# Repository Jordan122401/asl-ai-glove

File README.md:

# AI-Powered Glove for ASL Translation

> ESP32 + sensor glove + Android app that streams hand-sensor data over Bluetooth and runs on-device ML to translate ASL gestures into text.

---

## 📋 Quick Links

- 📱 **Android app:** [`android/`](android/)
- 🧠 **Firmware (ESP32):** [`firmware/esp32/`](firmware/esp32/)
- 🧰 **Calibration tools (Python):** [`tools/`](tools/)
- 🧾 **Docs (BLE + setup + calibration):** [`docs/`](docs/)
- 🧩 **Hardware (schematics/PCB):** [`hardware/`](hardware/)

---

## 🎥 Demo

### Video Demonstration

### 📸 Project Gallery

#### SignCast Logo & App Interface

**Glove in Action**

**Testing & Calibration**

<table>
  <tr>
    <td align="center" width="50%">
      
      <br><sub>Live sensor stream + calibration setup</sub>
    </td>
    <td align="center" width="50%">
      
      <br><sub>Gesture demo (GIF)</sub>
    </td>
  </tr>
</table>

---

## 🎯 System Overview

**Goal:** Translate ASL gestures using wearable sensors + embedded streaming + mobile ML inference.

### Pipeline Architecture

**How it works:**
1. **Glove sensors** (flex sensors + IMU) measure finger bend + motion
2. **ESP32 firmware** reads sensors and streams frames over Bluetooth
3. **Android app** receives frames, buffers a window, and runs on-device ML
4. App displays the predicted letter/gesture and can optionally do text-to-speech

#### System Architecture Diagram

#### Data Flow Diagram

---

## 🔧 Hardware

### 📐 Circuit Schematics

### 🖼️ PCB Design

### 📋 Bill of Materials

### 🔌 Wiring Guide

#### Wiring Diagram

#### Physical Wiring

---

## 💻 Software Components

### 📱 Android App (Kotlin)

**Location:** [`android/`](android/)

**Purpose:** Connects to the glove over Bluetooth, streams sensor data, runs on-device inference, and displays the predicted ASL output.

**Features:**
- Bluetooth discovery/connection + live streaming
- Buffers a **75-sample window** and runs the **BiLSTM + XGBoost fusion** model
- Displays prediction (optional text-to-speech if enabled)
- Loads model assets from `android/app/src/main/assets/`

**Setup Instructions:**
1. Open **`android/`** in Android Studio (File → Open → `android`)
2. Place model files in `android/app/src/main/assets/`:
   - `TFLiteCompatible_LSTM.tflite`
   - `TFLiteCompatible_XGB.json`
   - `labels.txt` (optional)
3. Plug in Android phone → **Run**

> 📖 Detailed connection steps: [`docs/BLUETOOTH_SETUP_GUIDE.md`](docs/BLUETOOTH_SETUP_GUIDE.md)

---

### 🔷 ESP32 Firmware

**Location:** [`firmware/esp32/`](firmware/esp32/)

**Purpose:** Reads glove sensors and streams frames over Bluetooth at a steady rate.

**Features:**
- Reads flex sensors + IMU values
- Packages frames for the Android app
- Streams continuously over Bluetooth

**Setup Instructions:**
1. Open the main `.ino` in Arduino IDE
2. Select your ESP32 board + COM port
3. Upload

---

### 🛠️ Calibration Tools (Python)

**Location:** [`tools/`](tools/)

**Purpose:** Helps collect/replay calibration data and generate calibration outputs used by the Android app.

**Typical Use:**
- Capture baseline + max bend values
- Export calibration results to .csv for consistent readings across sessions/users

---

## 🤖 Fusion Model (AI + ML)

**Model Architecture:** Hybrid (stacked) LSTM + XGBoost
- LSTM learns sequence features from sensor windows
- XGBoost refines the prediction using LSTM residual/error information

**Model Specifications:**
- **Input window:** 75 samples × 10 features  
  `flex1–flex5, roll_deg, pitch_deg, ax_g, ay_g, az_g`
- **Output classes:** 28 total  
  `A–Z + NEUTRAL + BACKSPACE`
- **Label encoding:** `A→0 ... Z→25, BACKSPACE→26, NEUTRAL→27`

**Model File Locations:**
- `android/app/src/main/assets/`
  - `TFLiteCompatible_LSTM.tflite`
  - `TFLiteCompatible_XGB.json`
  - `labels.txt` (optional; one label per line in index order)

---

## 📁 Repository Structure

This repo is organized as a clean monorepo:

```
├── android/              # Android Studio project
├── firmware/esp32/       # ESP32 Arduino sketch
├── hardware/            # Schematics, PCB exports, build files
├── docs/                # BLE, calibration, setup documentation
└── tools/               # Python scripts and helper utilities
```

---

## 📚 Documentation

**Essential Guides:**
- 🔗 Bluetooth Setup: [`docs/BLUETOOTH_SETUP_GUIDE.md`](docs/BLUETOOTH_SETUP_GUIDE.md)
- 📡 BLE Commands: [`docs/BLE_COMMAND_GUIDE.md`](docs/BLE_COMMAND_GUIDE.md)
- ⚙️ Calibration: [`docs/CALIBRATION_SIMPLIFIED.md`](docs/CALIBRATION_SIMPLIFIED.md)

---

## 🚀 Roadmap

- [ ] Improve dataset collection flow (more users, more sessions, better labeling + balancing)
- [ ] Expand gesture vocabulary and add "confusable letter" training (ex: **M vs N**, S vs A, etc.)
- [ ] **Hardware v2:** add more sensing points (additional flex sensors / fingertip pressure / better IMU placement) to improve accuracy on close hand shapes
- [ ] Reduce latency + improve stability filtering (smoother predictions, fewer flickers)
- [ ] Enclosure + strain relief + durability improvements (wearability + repeatable sensor placement)
- [ ] **VR integration (long-term):** adapt the glove as a VR input device (pose/gesture tracking + SDK integration)

---

## 👥 Credits

**Team Members:**
- Jordan Wray
- Madison Peterkin
- Raul Chavez
- Davaney Pierre
- Mark Louis

**Institution:** Engineering Design 2, Florida Atlantic University

**Acknowledgments:** Inspired by Cornell University ECE 4760 "Sign Language Translation" glove projects (sensor glove + ML translation concept)

---

<p align="center"><b>Made with ❤️ by the SignCast Team</b></p>

<p align="center">
  
  <br>
  <sub>Engineering Design 2 — SignCast Team (5 members)</sub>
</p>

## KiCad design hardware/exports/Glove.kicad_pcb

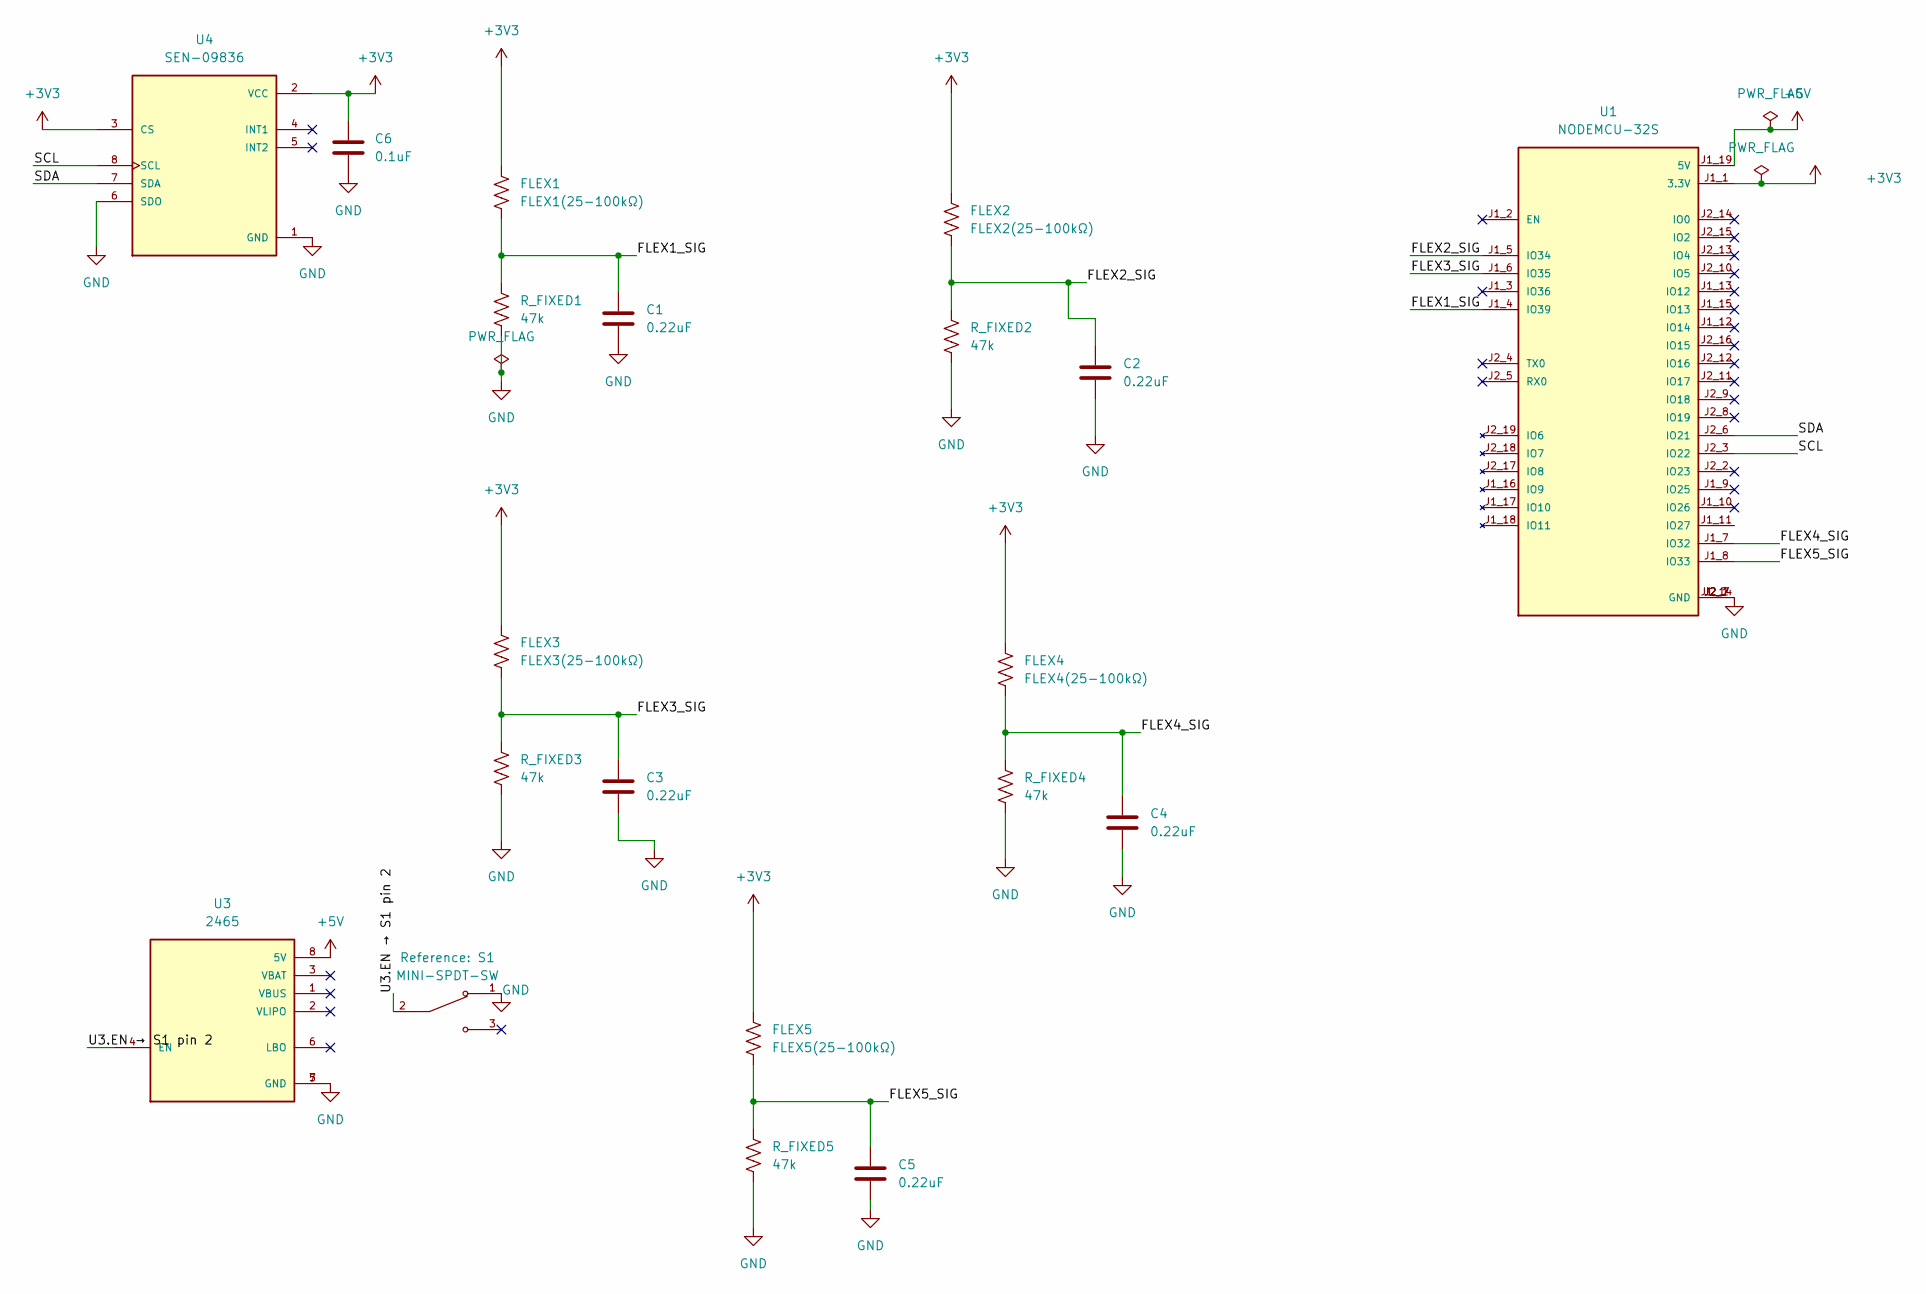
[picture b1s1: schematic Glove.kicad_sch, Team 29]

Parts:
C1, C2, C3, C4, C5: 0.22uF; C_Disc_D3.0mm_W2.0mm_P2.50mm
C6: 0.1uF; C_Disc_D3.0mm_W2.0mm_P2.50mm
FLEX1: FLEX1(25-100kΩ); Wire_2pad_P3.50_D1.40
FLEX2: FLEX2(25-100kΩ); Wire_2pad_P3.50_D1.40
FLEX3: FLEX3(25-100kΩ); Wire_2pad_P3.50_D1.40
FLEX4: FLEX4(25-100kΩ); Wire_2pad_P3.50_D1.40
FLEX5: FLEX5(25-100kΩ); Wire_2pad_P3.50_D1.40
R_FIXED1, R_FIXED2, R_FIXED3, R_FIXED4, R_FIXED5: 47k; R_Axial_DIN0207_L6.3mm_D2.5mm_P7.62mm_Horizontal
S1: MINI-SPDT-SW; Mini_SPDT(used); PARTREV C
U1: NODEMCU-32S; MODULE_NODEMCU-32S; PARTREV V1
U3: 2465; MODULE_2465; PARTREV B
U4: SEN-09836; MODULE_SEN-09836; PARTREV v14

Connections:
+3V3: C6.1, FLEX1.1, FLEX2.1, FLEX3.1, FLEX4.1, FLEX5.1, U1.J1_1 (3.3V), U4.2 (VCC), U4.3 (CS); also elsewhere on the board
+5V: U1.J1_19 (5V), U3.8 (5V)
/FLEX1_SIG: C1.1, FLEX1.2, R_FIXED1.1, U1.J1_4 (IO39)
/FLEX2_SIG: C2.1, FLEX2.2, R_FIXED2.1, U1.J1_5 (IO34)
/FLEX3_SIG: C3.1, FLEX3.2, R_FIXED3.1, U1.J1_6 (IO35)
/FLEX4_SIG: C4.1, FLEX4.2, R_FIXED4.1, U1.J1_7 (IO32)
/FLEX5_SIG: C5.1, FLEX5.2, R_FIXED5.1, U1.J1_8 (IO33)
/SCL: U1.J2_3 (IO22), U4.8 (SCL); also elsewhere on the board
/SDA: U1.J2_6 (IO21), U4.7 (SDA); also elsewhere on the board
/U3.EN → S1 pin 2: S1.2, U3.4 (EN)
GND: C1.2, C2.2, C3.2, C4.2, C5.2, C6.2, R_FIXED1.2, R_FIXED2.2, R_FIXED3.2, R_FIXED4.2, R_FIXED5.2, S1.1, U1.J1_14 (GND), U1.J2_1 (GND), U1.J2_7 (GND), U3.5 (GND), U3.7 (GND), U4.1 (GND), U4.6 (SDO); also elsewhere on the board

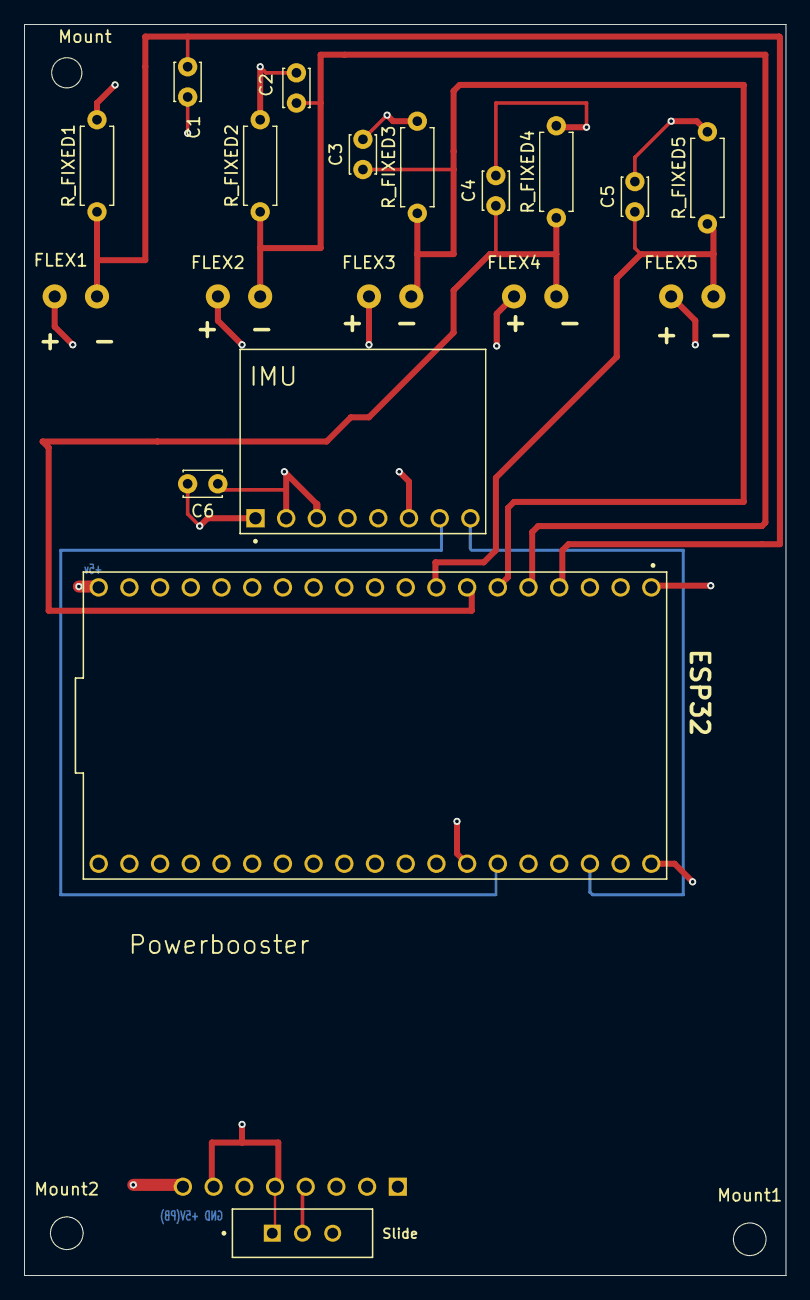
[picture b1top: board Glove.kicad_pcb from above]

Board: 4 copper layers, 63.0 x 103.5 mm, 23 parts (1 on the bottom side), 11 nets.

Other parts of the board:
Mount: MountingHole_2.5mm
Mount1, Mount2: MountingHole_2.7mm
U2: SEN-09836; MODULE_SEN-09836

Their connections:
+3V3: U2.2 (VCC), U2.3 (CS); also elsewhere on the board
/SCL: U2.8 (SCL); also elsewhere on the board
/SDA: U2.7 (SDA); also elsewhere on the board
GND: U2.1 (GND), U2.6 (SDO); also elsewhere on the board

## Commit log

2025-09-07 Initial commit of Android Studio project
2025-09-07 Added two views: main, and setttings.
2025-09-07 Added bluetooth view
2025-09-07 Changed some UI elements
2025-09-10 Main page update with logo, with litert added to help simulate a working program.
2025-09-11 Adding trained model TFLite file to assets
2025-09-11 Small updates to code and comments
2025-09-15 Some changes mainly for settings page
2025-10-09 Added a clear text button next to the connect text button.
2025-10-13 Completely reworked the old model to app integration to accommodate the fusion model.
2025-10-13 Added a demo for simulating glove hand gestures(Currently only shows B/D)
2025-10-13 Removed Demo Testing, and added bluetooth functionality for connecting to the glove.
2025-10-21 Created user selection screen allowing a user to calibrate the glove and save it to a user account. Calibration should follow the "trial_capture_logger.py".
2025-10-27 Bluetooth functionality updates and fixes
2025-10-29 Updated bluetooth paired devices to show as black text. Added a command log screen with a text box to send commands.
2025-10-29 Minor UI Updates to the calibration page and command log page for simplicity.
2025-10-29 More UI updates and new ASL_BLE file
2025-10-29 More UI updates
2025-10-29 Complete user overhaul with pre-defined users, functioning AI model letter prediction for letters A-D.
2025-10-29 Startup page, main page, and settings page overhaul for seemless transitions throughout the app for the user.
2025-10-29 Updated main page "Start Stream" button functionality to work correctly if glove is already connected, and no more TTS when letters are appended.
2025-11-26 Letters A-I work
2025-12-01 All letters: A-Z
2025-12-03 Updated model with remixed MXC + backspace
2025-12-03 Removed backspace from model
2025-12-03 Added backspace back to model
2025-12-03 Added backspace model back
2025-12-03 Fix cut off text
2025-12-08 Add hardware folder with schematic and PCB
2025-12-15 Add AGENTS.md for Codex instructions
2025-12-15 Restructure repository layout and documentation
2025-12-15 Update README and project organization
